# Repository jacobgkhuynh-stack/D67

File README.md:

# Diodeless-Keyboard with 67 keys in a 65% layout
So here's what this is, a Diodeless Keyboard that uses graph theory like Triliu's JESK56 keyboard https://github.com/triliu/JESK56 but using a different graph https://houseofgraphs.org/graphs/49999.
The nodes are pins and the vertices of the graph are switches using this method and placing them in a way can make it so that practically when using the board it feels like a n-key-rollover board even though it' actually only 4-key-rollover
I made this for week 5 of Hack Club's Halflife program.
I have no clue if it works but it took a ton of time.
Oh yeah, you can replace the 2 keys near the bottom right with a oled display if you wanted

Here's a BoM
|Item                    |Qty|Supplier                   |Cost/item|Total Cost|link                                                                                                                                                                                                                                                                                                                                                                                                                                                                                                                                                                                                                                                          |
|------------------------|---|---------------------------|---------|----------|--------------------------------------------------------------------------------------------------------------------------------------------------------------------------------------------------------------------------------------------------------------------------------------------------------------------------------------------------------------------------------------------------------------------------------------------------------------------------------------------------------------------------------------------------------------------------------------------------------------------------------------------------------------|
|PCB                     |1  |JLCPCB                     |$12.60   |$12.60    |https://jlcpcb.com/                                                                                                                                                                                                                                                                                                                                                                                                                                                                                                                                                                                                                                           |
|Keyboard Switches 70 pcs|1  |uluky Lifestyle Store Store|$20.94   |$20.94    |https://www.aliexpress.us/item/3256804099108371.html?spm=a2g0o.productlist.main.2.3cac317a2owKIp&algo_pvid=5f8ed487-6467-4458-a060-eeb4f17860b8&algo_exp_id=5f8ed487-6467-4458-a060-eeb4f17860b8-1&pdp_ext_f=%7B%22order%22%3A%2214215%22%2C%22eval%22%3A%221%22%2C%22fromPage%22%3A%22search%22%7D&pdp_npi=6%40dis%21USD%212.81%211.09%21%21%212.81%211.09%21%402101c69517941872517192815e0f84%2112000028628937388%21sea%21US%210%21ABX%211%210%21n_tag%3A-29910%3Bd%3A92917014%3Bm03_new_user%3A-29895%3BpisId%3A5000000218032551&curPageLogUid=t4moLjC3xkMt&utparam-url=scene%3Asearch%7Cquery_from%3A%7Cx_object_id%3A1005004285423123%7C_p_origin_prod%3A|
|RP2350B devboard        |1  |Raysunny Store             |$8.85    |$8.85     |https://www.aliexpress.us/item/3256813259480447.html?spm=a2g0o.productlist.main.13.7673d38eN5HOTy&algo_pvid=b539468f-5144-45ac-851c-c5c25f87c9ae&algo_exp_id=b539468f-5144-45ac-851c-c5c25f87c9ae-12&pdp_ext_f=%7B%22order%22%3A%22-1%22%2C%22eval%22%3A%221%22%2C%22fromPage%22%3A%22search%22%7D&pdp_npi=6%40dis%21USD%2121.08%218.85%21%21%21139.79%2158.71%21%40210327b017941874379806831e0c27%2112000061145069145%21sea%21US%210%21ABX%211%210%21n_tag%3A-29910%3Bd%3A92917014%3Bm03_new_user%3A-29895&curPageLogUid=asxl3dmPupIl&utparam-url=scene%3Asearch%7Cquery_from%3A%7Cx_object_id%3A1005013445795199%7C_p_origin_prod%3A                        |
|Estimated total shipping|1  |                           |         |$20.02    |                                                                                                                                                                                                                                                                                                                                                                                                                                                                                                                                                                                                                                                              |

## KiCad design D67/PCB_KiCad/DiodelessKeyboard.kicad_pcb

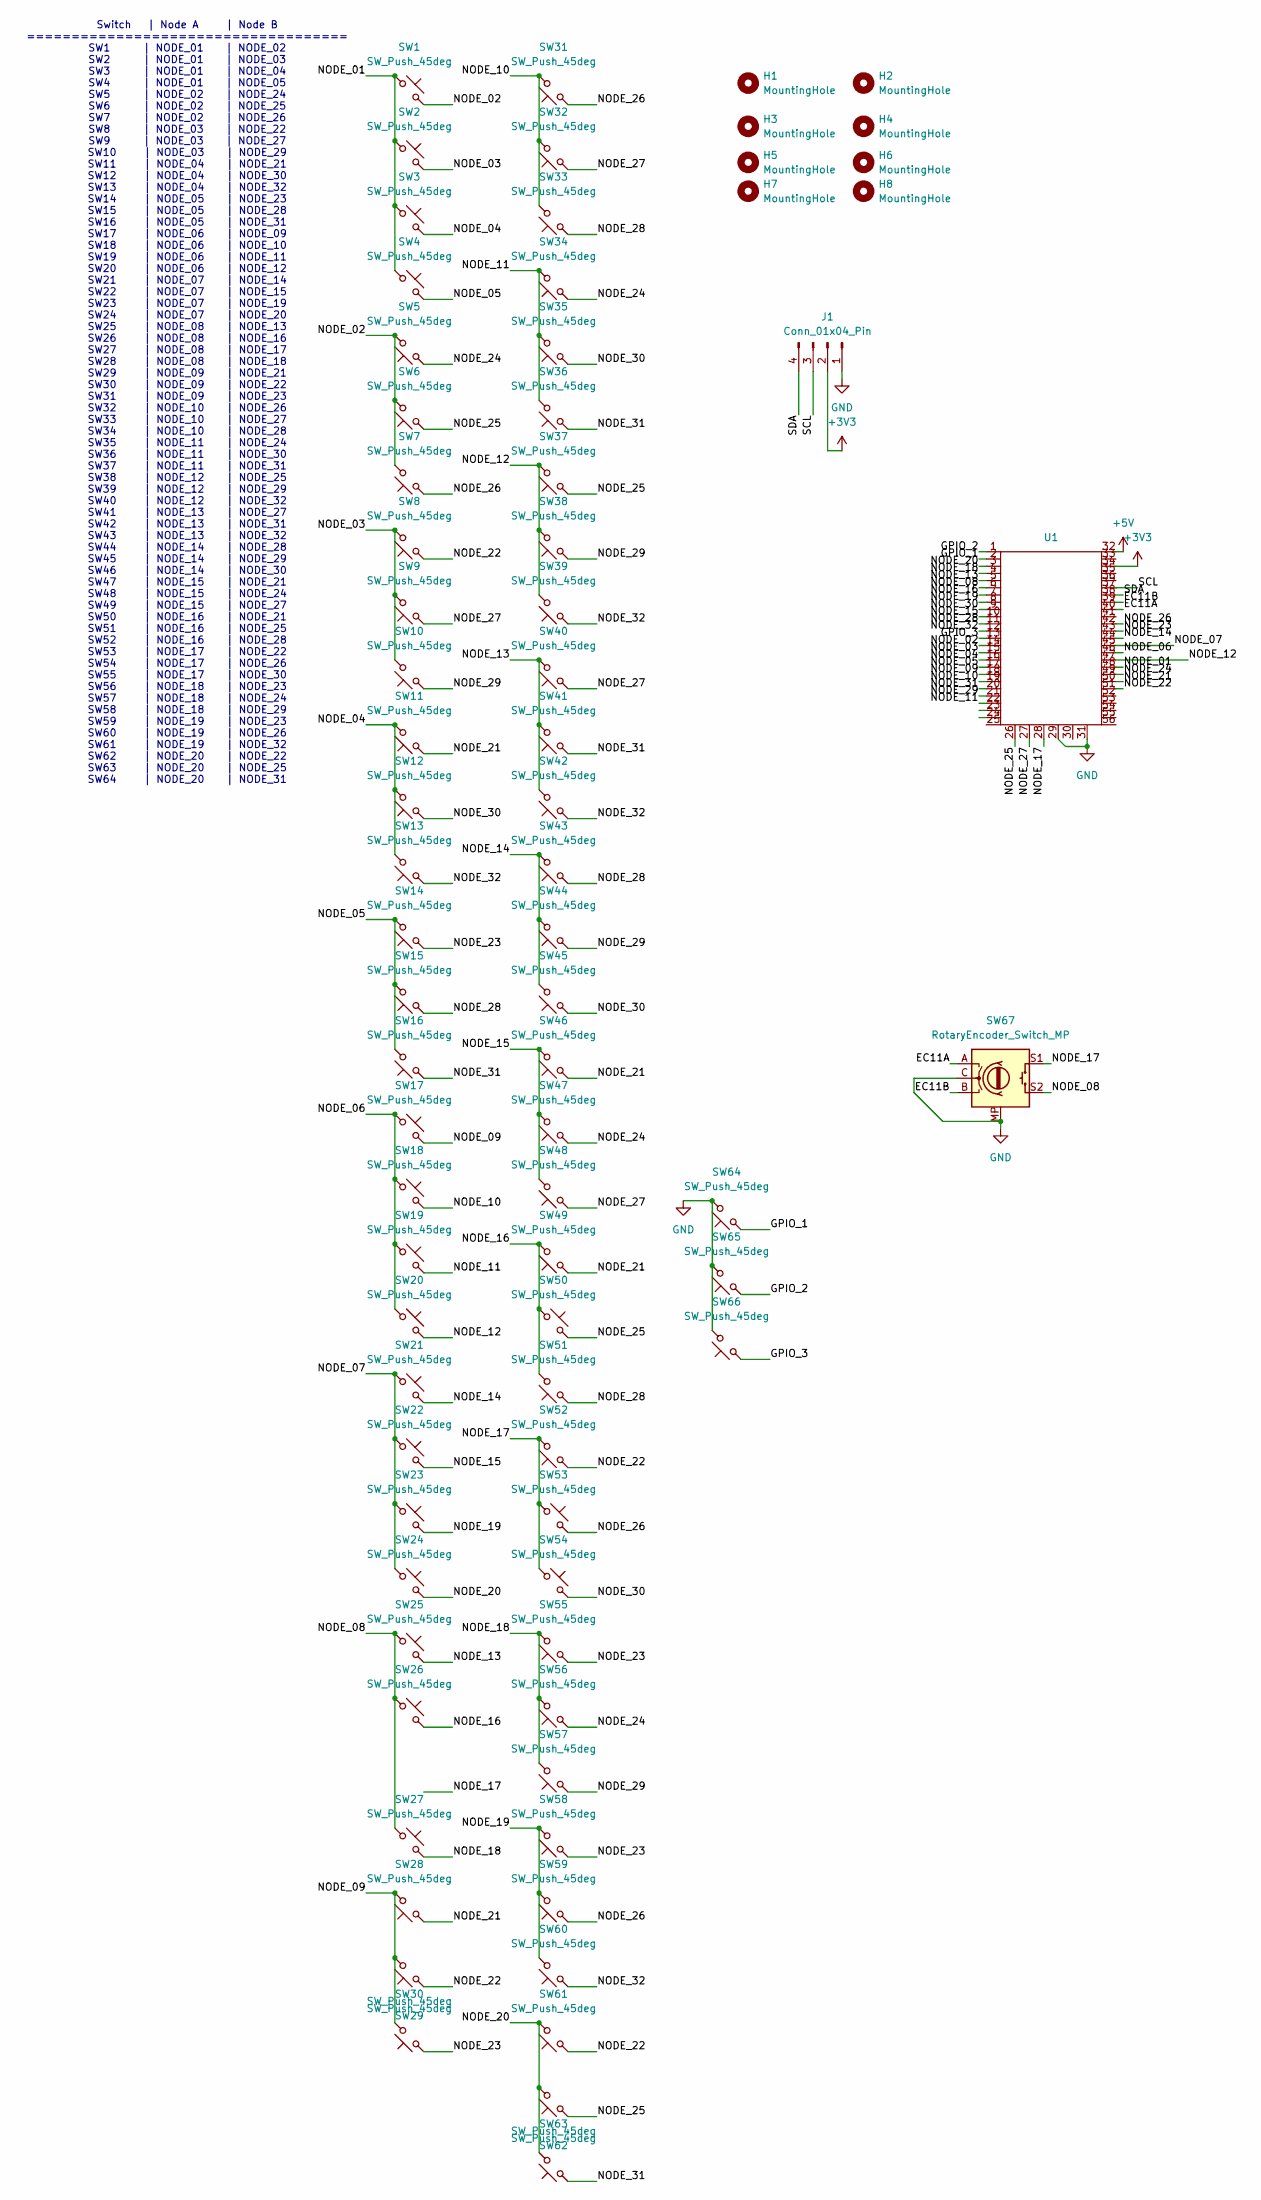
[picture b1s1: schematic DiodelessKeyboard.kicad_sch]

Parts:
H1, H2, H3, H4, H5, H6, H7, H8: MountingHole; MountingHole_2.7mm_M2.5
J1: Conn_01x04_Pin; PinHeader_1x04_P2.54mm_Vertical
SW1, SW2, SW3, SW4, SW8, SW9, SW10, SW11, SW12, SW13, SW14, SW15, SW16, SW17, SW18, SW19, SW20, SW21, SW22, SW23, SW24, SW25, SW28, SW29, SW30, SW31, SW32, SW33, SW34, SW35, SW36, SW37, SW38, SW39, SW40, SW42, SW43, SW44, SW45, SW46, SW47, SW48, SW52, SW55, SW56, SW57, SW58, SW59, SW60, SW61, SW62, SW64, SW65: SW_Push_45deg; SW_Cherry_MX_1.00u_PCB
SW5, SW49: SW_Push_45deg; SW_Cherry_MX_1.50u_PCB
SW6, SW63: SW_Push_45deg; SW_Cherry_MX_1.75u_PCB
SW7, SW41: SW_Push_45deg; SW_Cherry_MX_2.25u_PCB
SW26: SW_Push_45deg; SW_Cherry_MX_2.00u_PCB
SW27, SW50, SW51, SW53, SW54: SW_Push_45deg; SW_Cherry_MX_1.25u_PCB
SW66: SW_Push_45deg; SW_Cherry_MX_6.25u_PCB
SW67: RotaryEncoder_Switch_MP; RotaryEncoder_Alps_EC11E-Switch_Vertical_H20mm
U1: Raspberry-Pi-Pico-2-RP2350-Linux-MINI-RP2350B-USB

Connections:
+3V3: J1.2, U1.34
+5V: U1.32
/EC11A: SW67.A, U1.40
/EC11B: SW67.B, U1.39
/GPIO_1: SW64.1, U1.2
/GPIO_2: SW65.1, U1.1
/GPIO_3: SW66.1, U1.13
/NODE_01: SW1.1, SW2.1, SW3.1, SW4.1, U1.48
/NODE_02: SW1.2, SW5.2, SW6.2, SW7.2, U1.14
/NODE_03: SW2.2, SW8.2, SW9.2, SW10.2, U1.15
/NODE_04: SW3.2, SW11.2, SW12.2, SW13.2, U1.16
/NODE_05: SW4.2, SW14.2, SW15.2, SW16.2, U1.17
/NODE_06: SW17.1, SW18.1, SW19.1, SW20.1, U1.46
/NODE_07: SW21.1, SW22.1, SW23.1, SW24.1, U1.45
/NODE_08: SW25.1, SW26.1, SW27.1, SW67.S2, U1.6
/NODE_09: SW17.2, SW28.2, SW29.2, SW30.2, U1.18
/NODE_10: SW18.2, SW31.2, SW32.2, SW33.2, U1.19
/NODE_11: SW19.2, SW34.2, SW35.2, SW36.2, U1.22
/NODE_12: SW20.2, SW37.2, SW38.2, SW39.2, U1.47
/NODE_13: SW25.2, SW40.2, SW41.2, SW42.2, U1.5
/NODE_14: SW21.2, SW43.2, SW44.2, SW45.2, U1.44
/NODE_15: SW22.2, SW46.2, SW47.2, SW48.2, U1.10
/NODE_16: SW26.2, SW49.2, SW50.1, SW51.2, U1.7
/NODE_17: SW52.2, SW53.1, SW54.1, SW67.S1, U1.28
/NODE_18: SW27.2, SW55.2, SW56.2, SW57.2, U1.4
/NODE_19: SW23.2, SW58.2, SW59.2, SW60.2, U1.8
/NODE_20: SW24.2, SW61.2, SW62.2, SW63.2, U1.3
/NODE_21: SW11.1, SW28.1, SW46.1, SW49.1, U1.50
/NODE_22: SW8.1, SW29.1, SW52.1, SW61.1, U1.51
/NODE_23: SW14.1, SW30.1, SW55.1, SW58.1, U1.43
/NODE_24: SW5.1, SW34.1, SW47.1, SW56.1, U1.49
/NODE_25: SW6.1, SW37.1, SW50.2, SW62.1, U1.26
/NODE_26: SW7.1, SW31.1, SW53.2, SW59.1, U1.42
/NODE_27: SW9.1, SW32.1, SW40.1, SW48.1, U1.27
/NODE_28: SW15.1, SW33.1, SW43.1, SW51.1, U1.11
/NODE_29: SW10.1, SW38.1, SW44.1, SW57.1, U1.21
/NODE_30: SW12.1, SW35.1, SW45.1, SW54.2, U1.9
/NODE_31: SW16.1, SW36.1, SW41.1, SW63.1, U1.20
/NODE_32: SW13.1, SW39.1, SW42.1, SW60.1, U1.12
/SCL: J1.3, U1.37
/SDA: J1.4, U1.38
GND: J1.1, SW64.2, SW65.2, SW66.2, SW67.C, SW67.MP, U1.29, U1.31

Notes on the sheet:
Switch | Node A | Node B ==================================== SW1 | NODE_01 | NODE_02 SW2 | NODE_01 | NODE_03 SW3 | NODE_01 | NODE_04 SW4 | NODE_01 | NODE_05 SW5 | NODE_02 | NODE_24 SW6 | NODE_02 | NODE_25 SW7 | NODE_02 | NODE_26 SW8 | NODE_03 | NODE_22 SW9 | NODE_03 | NODE_27 SW10 | NODE_03 | NODE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

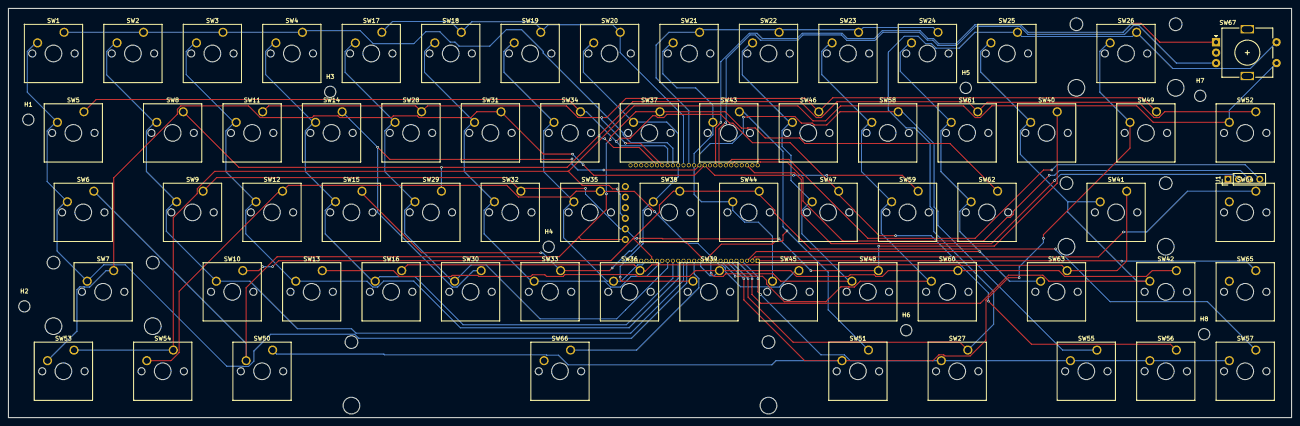
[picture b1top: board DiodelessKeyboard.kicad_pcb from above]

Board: 2 copper layers, 307.7 x 98.1 mm, 77 parts (1 on the bottom side), 41 nets.

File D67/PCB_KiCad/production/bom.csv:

Designator,Footprint,Quantity,Value,LCSC Part #
J1,PinHeader_1x04_P2.54mm_Vertical,1,Conn_01x04_Pin,
"SW1, SW10, SW11, SW12, SW13, SW14, SW15, SW16, SW17, SW18, SW19, SW2, SW20, SW21, SW22, SW23, SW24, SW25, SW28, SW29, SW3, SW30, SW31, SW32, SW33, SW34, SW35, SW36, SW37, SW38, SW39, SW4, SW40, SW42, SW43, SW44, SW45, SW46, SW47, SW48, SW52, SW55, SW56, SW57, SW58, SW59, SW60, SW61, SW62, SW64, SW65, SW8, SW9",SW_Cherry_MX_1.00u_PCB,53,SW_Push_45deg,
SW26,SW_Cherry_MX_2.00u_PCB,1,SW_Push_45deg,
"SW27, SW50, SW51, SW53, SW54",SW_Cherry_MX_1.25u_PCB,5,SW_Push_45deg,
"SW41, SW7",SW_Cherry_MX_2.25u_PCB,2,SW_Push_45deg,
"SW49, SW5",SW_Cherry_MX_1.50u_PCB,2,SW_Push_45deg,
"SW6, SW63",SW_Cherry_MX_1.75u_PCB,2,SW_Push_45deg,
SW66,SW_Cherry_MX_6.25u_PCB,1,SW_Push_45deg,
SW67,RotaryEncoder_Alps_EC11E-Switch_Vertical_H20mm,1,RotaryEncoder_Switch_MP,
U1,Raspberry-Pi-Pico-2-RP2350-Linux-MINI-RP2350B-USB,1,~,
